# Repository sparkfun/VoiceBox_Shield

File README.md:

SparkFun VoiceBox Shield
========================================

[*SparkFun VoiceBox Shield (DEV-10661)*](https://www.sparkfun.com/products/10661)

The SparkFun VoiceBox Shield can be mounted on top of your Arduino board to give it access to all of the capabilities of the SpeakJet voice and sound synthesizer. 
The Voice Box Shield uses the SpeakJet chip to convert serial commands into a great robot-sounding voice.

Repository Contents
-------------------

* **/Firmware** - Example code 
* **/Hardware** - Eagle design files (.brd, .sch)
* **/Production** - Production panel files (.brd)

Documentation
--------------
* **[Hookup Guide](https://www.sparkfun.com/tutorials/285)** - Basic hookup guide for the VoiceBox Shield.
* **[SparkFun Fritzing repo](https://github.com/sparkfun/Fritzing_Parts)** - Fritzing diagrams for SparkFun products.
* **[SparkFun 3D Model repo](https://github.com/sparkfun/3D_Models)** - 3D models of SparkFun products. 

License Information
-------------------
This product is _**open source**_! 

The **hardware** is released under [Creative Commons ShareAlike 4.0 International](https://creativecommons.org/licenses/by-sa/4.0/).

The **code** is beerware; if you see me (or any other SparkFun employee) at the local, and you've found our code helpful, please buy us a round!

Please use, reuse, and modify these files as you see fit. Please maintain attribution to SparkFun Electronics and release anything derivative under the same license.

Distributed as-is; no warranty is given.

- Your friends at SparkFun.

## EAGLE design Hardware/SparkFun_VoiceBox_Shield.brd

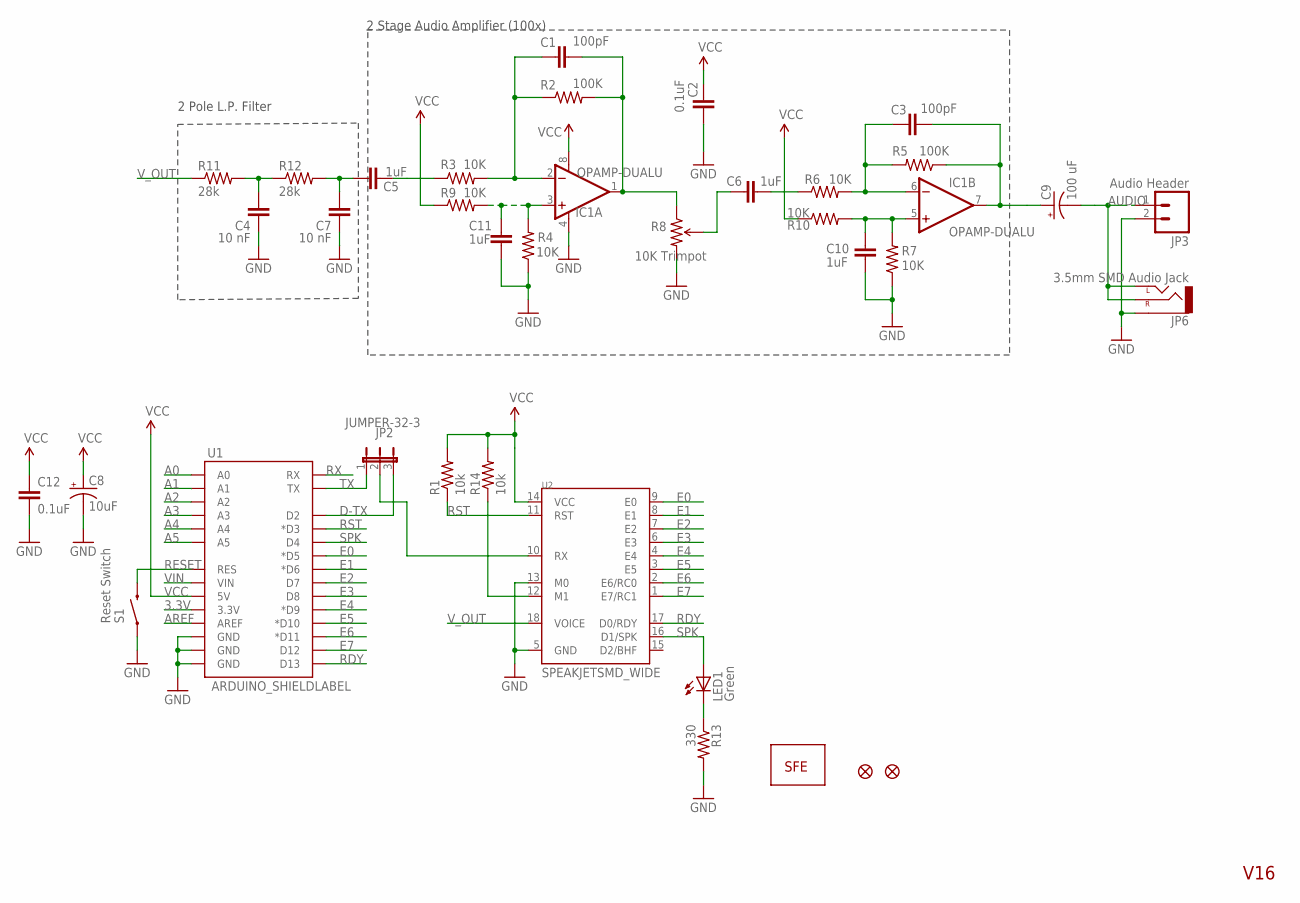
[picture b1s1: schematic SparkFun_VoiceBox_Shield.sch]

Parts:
C1, C3: 100pF; 0603-CAP
C2, C12: 0.1uF; 0603-CAP
C4, C7: 10 nF; 0603-CAP
C5, C6, C10, C11: 1uF; 0603-CAP
C8: 10uF; EIA3216
C9: 100 uF; EIA7343
IC1: OPAMP-DUALU; SO08
JP1: LOGO-SFENEW; SFE-NEW-WEBLOGO
JP2: JUMPER-32-3; SJ_3_PASTE2&3
JP3: Audio Header; 1X02
JP4, JP5: FIDUCIAL1X2; FIDUCIAL-1X2
JP6: 3.5mm SMD Audio Jack; AUDIO-JACK-3.5MM-SMD
LED1: Green; LED-0603
R1, R14: 10k; 0603-RES
R2, R5: 100K; 0603-RES
R3, R4, R6, R7: 10K; 0603-RES
R8: 10K Trimpot; TRIMPOT-3MM
R9, R10: 10K; 0603
R11, R12: 28k; 0603-RES
R13: 330; 0603-RES
S1: Reset Switch; TACTILE_SWITCH_SMD
U1: ARDUINO_SHIELDLABEL; DUEMILANOVE_SHIELD
U2: SPEAKJETSMD_WIDE; SO-18W

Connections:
3.3V: U1.3.3V
A0: U1.A0
A1: U1.A1
A2: U1.A2
A3: U1.A3
A4: U1.A4
A5: U1.A5
AREF: U1.AREF
AUDIO: C9.C (-), JP3.1, JP6.RING (RIGHT), JP6.TIP (LEFT)
D-TX: JP2.3, U1.D2
E0: U1.D5 (*D5), U2.9 (E0)
E1: U1.D6 (*D6), U2.8 (E1)
E2: U1.D7, U2.7 (E2)
E3: U1.D8, U2.6 (E3)
E4: U1.D9 (*D9), U2.4 (E4)
E5: U1.D10 (*D10), U2.3 (E5)
E6: U1.D11 (*D11), U2.2 (E6/RC0)
E7: U1.D12, U2.1 (E7/RC1)
GND: C2.2, C4.1, C7.1, C8.C (-), C10.2, C11.2, C12.2, IC1.4 (V-), JP3.2, JP6.SLEEVE, R4.1, R7.1, R8.3 (CW), R13.2, S1.1, U1.GND@0 (GND), U1.GND@1 (GND), U1.GND@2 (GND), U2.5 (GND), U2.13 (M0)
IN1: C5.2, R3.1
unnamed: JP2.2, U2.10 (RX)
unnamed: C1.1, IC1.2 (-IN), R2.1, R3.2
unnamed: C6.1, R6.1
unnamed: C6.2, R8.2 (WIPER)
unnamed: C3.1, IC1.6 (-IN), R5.2, R6.2
unnamed: C10.1, IC1.5 (+IN), R7.2, R10.2
unnamed: C11.1, IC1.3 (+IN), R4.2, R9.2
unnamed: C4.2, R11.2, R12.1
unnamed: C5.1, C7.2, R12.2
unnamed: LED1.C, R13.1
unnamed: R14.1, U2.12 (M1)
OUT1: C1.2, IC1.1 (OUT), R2.2, R8.1 (CCW)
RDY: U1.D13, U2.17 (D0/RDY)
RESET: S1.3 (2), U1.RES
RST: R1.1, U1.D3 (*D3), U2.11 (RST)
RX: U1.RX
SPK: LED1.A, U1.D4, U2.16 (D1/SPK)
SPK+: C3.2, C9.A (+), IC1.7 (OUT), R5.1
TX: JP2.1, U1.TX
VCC: C2.1, C8.A (+), C12.1, IC1.8 (V+), R1.2, R9.1, R10.1, R14.2, U1.5V, U2.14 (VCC)
VIN: U1.VIN
V_OUT: R11.1, U2.18 (VOICE)

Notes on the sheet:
2 Pole L.P. Filter
2 Stage Audio Amplifier (100x)
V16

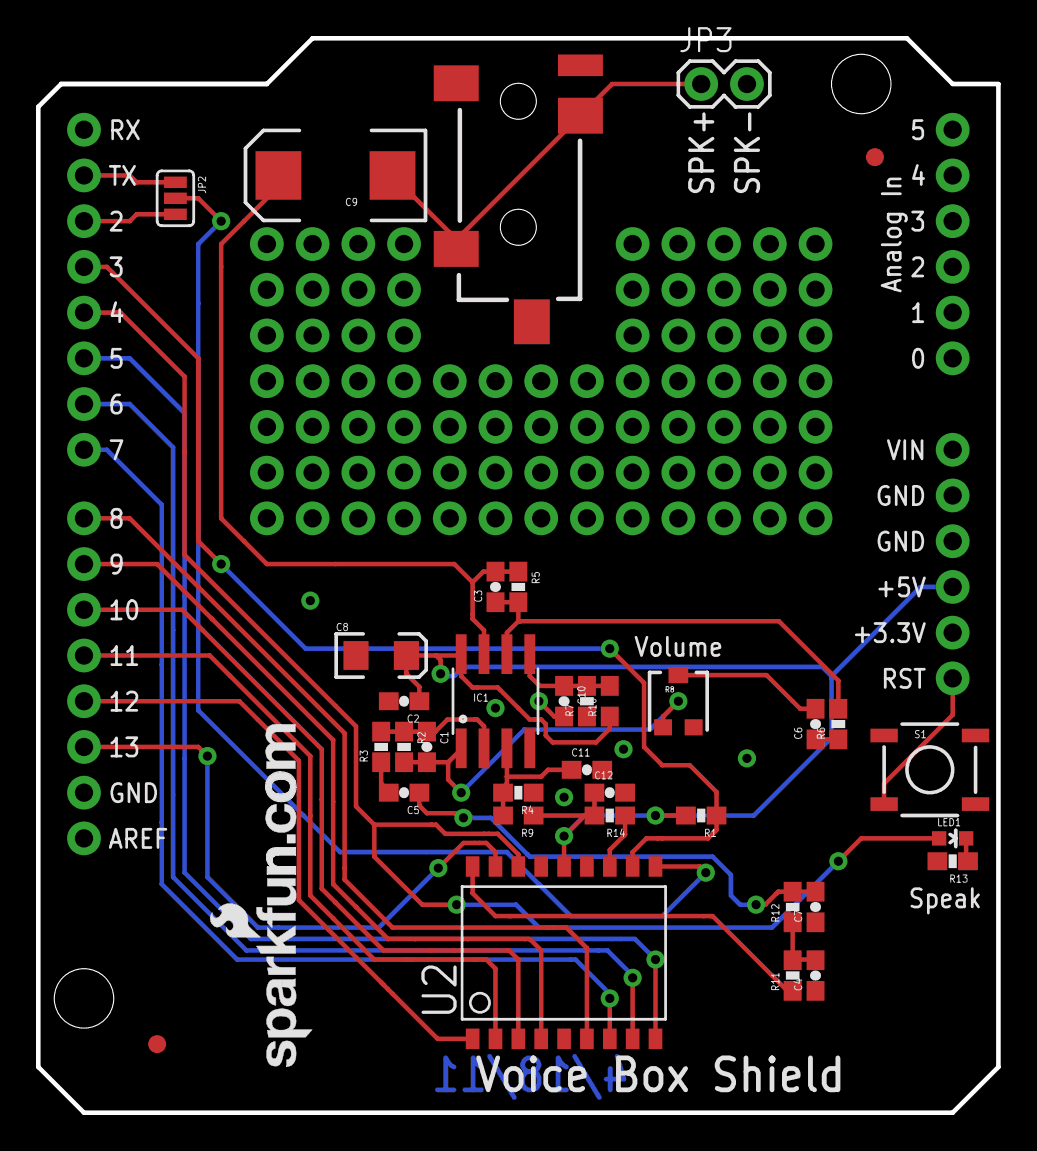
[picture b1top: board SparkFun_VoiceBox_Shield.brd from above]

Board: 2 copper layers, 53.3 x 59.7 mm, 37 parts (0 on the bottom side), 32 nets.

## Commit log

2015-05-11 Adding hardware and example sketch
